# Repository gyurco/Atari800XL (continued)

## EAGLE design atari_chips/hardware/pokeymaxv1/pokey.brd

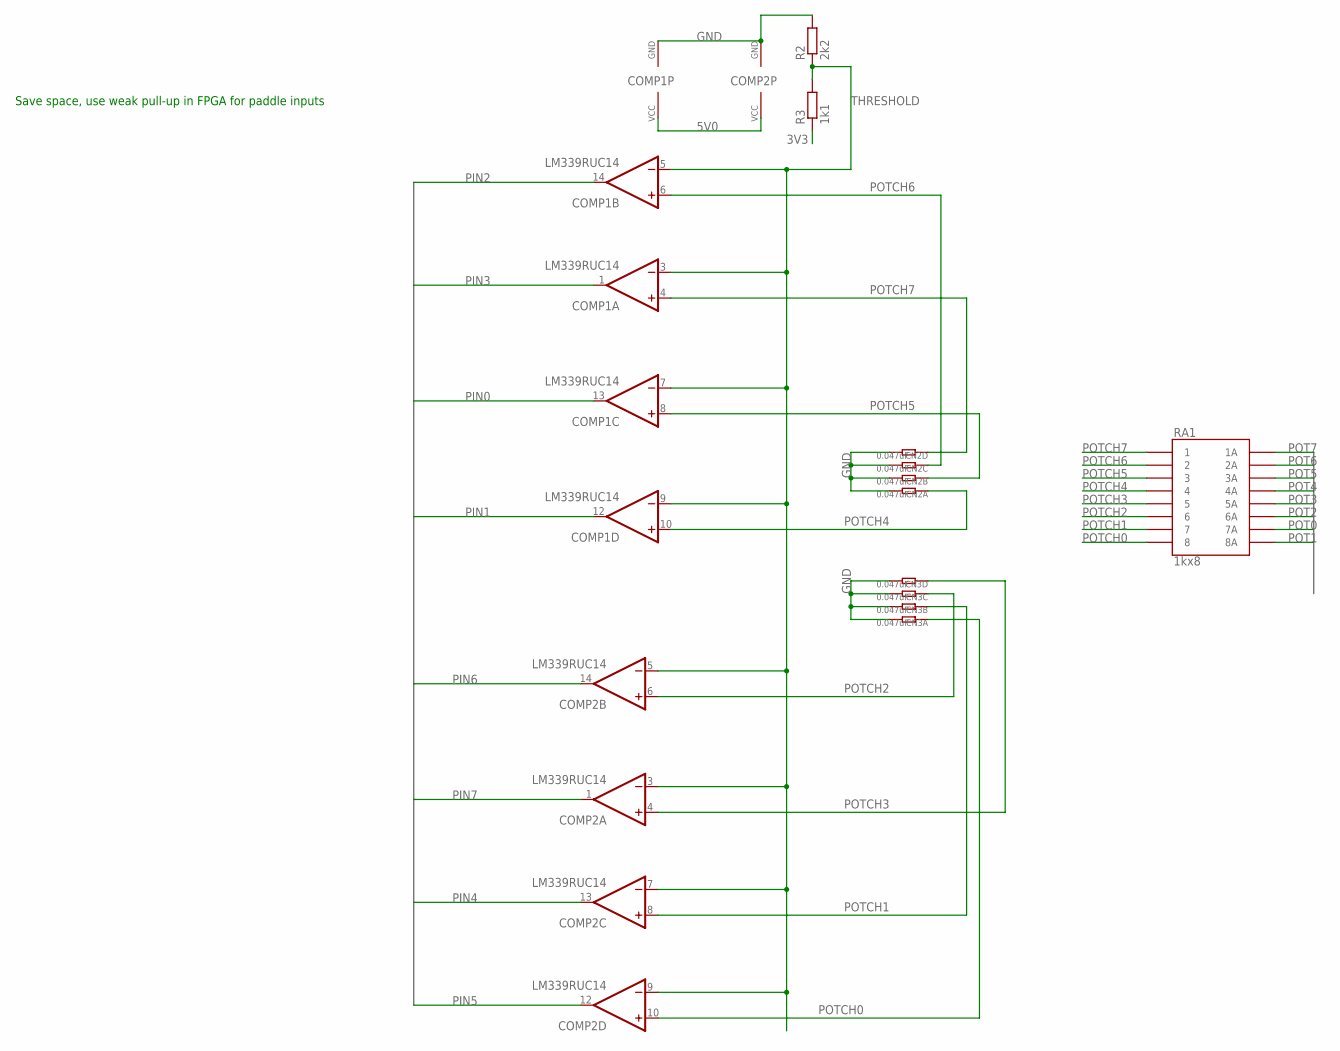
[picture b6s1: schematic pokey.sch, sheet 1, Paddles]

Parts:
CN2, CN3: 0.047uF; R1206-8
COMP1, COMP2: LM339RUC14; RUC14
R2: 2k2; R0603
R3: 1k1; R0603
RA1: 1kx8; CAY16-J8

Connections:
3V3: R3.1; also elsewhere on the board
5V0: COMP1.2 (VCC), COMP2.2 (VCC); also elsewhere on the board
GND: CN2.5 (2), CN2.6 (2), CN2.7 (2), CN2.8 (2), CN3.5 (2), CN3.6 (2), CN3.7 (2), CN3.8 (2), COMP1.11 (GND), COMP2.11 (GND), R2.2; also elsewhere on the board
PIN0: COMP1.13 (OUT); also elsewhere on the board
PIN1: COMP1.12 (OUT); also elsewhere on the board
PIN2: COMP1.14 (OUT); also elsewhere on the board
PIN3: COMP1.1 (OUT); also elsewhere on the board
PIN4: COMP2.13 (OUT); also elsewhere on the board
PIN5: COMP2.12 (OUT); also elsewhere on the board
PIN6: COMP2.14 (OUT); also elsewhere on the board
PIN7: COMP2.1 (OUT); also elsewhere on the board
POT0: RA1.P$10 (7A); also elsewhere on the board
POT1: RA1.P$9 (8A); also elsewhere on the board
POT2: RA1.P$11 (6A); also elsewhere on the board
POT3: RA1.P$12 (5A); also elsewhere on the board
POT4: RA1.P$13 (4A); also elsewhere on the board
POT5: RA1.P$14 (3A); also elsewhere on the board
POT6: RA1.P$15 (2A); also elsewhere on the board
POT7: RA1.P$16 (1A); also elsewhere on the board
POTCH0: CN3.1, COMP2.10 (+IN), RA1.P$8 (8); also elsewhere on the board
POTCH1: CN3.2 (1), COMP2.8 (+IN), RA1.P$7 (7); also elsewhere on the board
POTCH2: CN3.3 (1), COMP2.6 (+IN), RA1.P$6 (6); also elsewhere on the board
POTCH3: CN3.4 (1), COMP2.4 (+IN), RA1.P$5 (5); also elsewhere on the board
POTCH4: CN2.1, COMP1.10 (+IN), RA1.P$4 (4); also elsewhere on the board
POTCH5: CN2.2 (1), COMP1.8 (+IN), RA1.P$3 (3); also elsewhere on the board
POTCH6: CN2.3 (1), COMP1.6 (+IN), RA1.P$2 (2); also elsewhere on the board
POTCH7: CN2.4 (1), COMP1.4 (+IN), RA1.P$1 (1); also elsewhere on the board
THRESHOLD: COMP1.3 (-IN), COMP1.5 (-IN), COMP1.7 (-IN), COMP1.9 (-IN), COMP2.3 (-IN), COMP2.5 (-IN), COMP2.7 (-IN), COMP2.9 (-IN), R2.1, R3.2

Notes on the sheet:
Save space, use weak pull-up in FPGA for paddle inputs

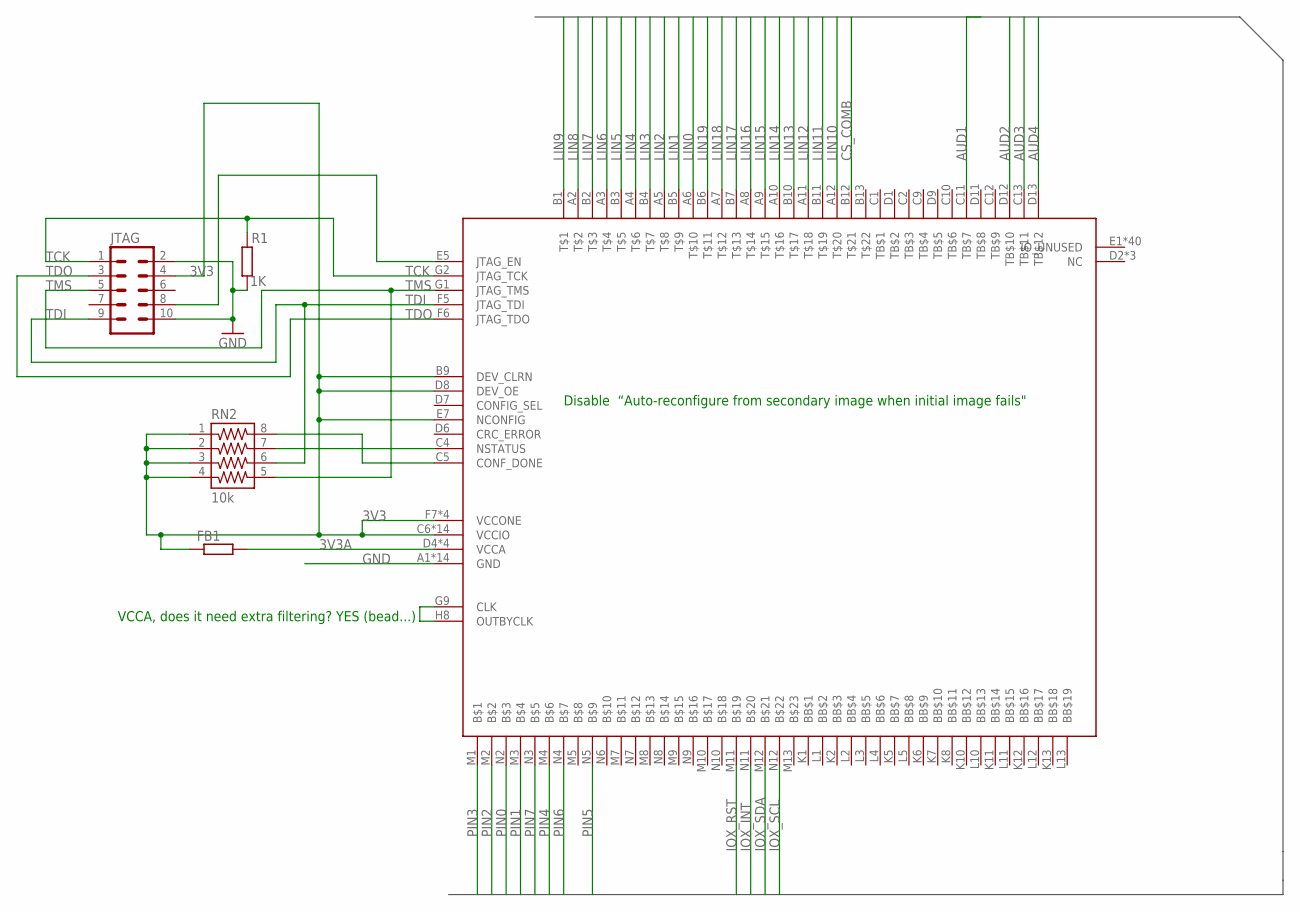
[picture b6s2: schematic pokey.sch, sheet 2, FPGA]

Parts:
FB1: R-EU_R0603; R0603
JTAG: ML10
MAX10: MAX10; U169SMALL
R1: 1K; R0603
RN2: 10k; 742-8

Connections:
3V3: FB1.1, JTAG.4, MAX10.B9 (DEV_CLRN), MAX10.C6 (VCCIO), MAX10.C7 (VCCIO), MAX10.C8 (VCCIO), MAX10.D8 (DEV_OE), MAX10.E7 (NCONFIG), MAX10.F2 (VCCIO), MAX10.F7 (VCCONE), MAX10.F11 (VCCIO), MAX10.G3 (VCCIO), MAX10.G6 (VCCONE), MAX10.G8 (VCCONE), MAX10.G11 (VCCIO), MAX10.H7 (VCCONE), MAX10.H11 (VCCIO), MAX10.J3 (VCCIO), MAX10.J11 (VCCIO), MAX10.K3 (VCCIO), MAX10.L6 (VCCIO), MAX10.L7 (VCCIO), MAX10.L8 (VCCIO), RN2.1, RN2.2, RN2.3, RN2.4; also elsewhere on the board
3V3A: FB1.2, MAX10.D4 (VCCA), MAX10.D10 (VCCA), MAX10.K4 (VCCA), MAX10.K9 (VCCA); also elsewhere on the board
AUD1: MAX10.C11 (TB$7); also elsewhere on the board
AUD2: MAX10.D12 (TB$10); also elsewhere on the board
AUD3: MAX10.C13 (TB$11); also elsewhere on the board
AUD4: MAX10.D13 (TB$12); also elsewhere on the board
CONF_DONE: MAX10.C5 (CONF_DONE), RN2.8
CS_COMB: MAX10.B12; also elsewhere on the board
FAKE_CLK: MAX10.G9 (CLK), MAX10.H8 (OUTBYCLK)
GND: JTAG.2, JTAG.10, MAX10.A1 (GND), MAX10.A13 (GND), MAX10.B8 (GND), MAX10.C3 (GND), MAX10.D5 (GND), MAX10.E11 (GND), MAX10.F3 (GND), MAX10.G7 (GND), MAX10.H12 (GND), MAX10.J4 (GND), MAX10.L9 (GND), MAX10.M6 (GND), MAX10.N1 (GND), MAX10.N13 (GND), R1.2; also elsewhere on the board
IOX_INT: MAX10.N11; also elsewhere on the board
IOX_RST: MAX10.M11; also elsewhere on the board
IOX_SCL: MAX10.N12; also elsewhere on the board
IOX_SDA: MAX10.M12; also elsewhere on the board
JTAGEN: JTAG.8, MAX10.E5 (JTAG_EN)
LIN0: MAX10.A6; also elsewhere on the board
LIN1: MAX10.B5; also elsewhere on the board
LIN2: MAX10.A5; also elsewhere on the board
LIN3: MAX10.B4; also elsewhere on the board
LIN4: MAX10.A4; also elsewhere on the board
LIN5: MAX10.B3; also elsewhere on the board
LIN6: MAX10.A3; also elsewhere on the board
LIN7: MAX10.B2; also elsewhere on the board
LIN8: MAX10.A2; also elsewhere on the board
LIN9: MAX10.B1; also elsewhere on the board
LIN10: MAX10.A12; also elsewhere on the board
LIN11: MAX10.B11; also elsewhere on the board
LIN12: MAX10.A11; also elsewhere on the board
LIN13: MAX10.B10; also elsewhere on the board
LIN14: MAX10.A10; also elsewhere on the board
LIN15: MAX10.A9; also elsewhere on the board
LIN16: MAX10.A8; also elsewhere on the board
LIN17: MAX10.B7; also elsewhere on the board
LIN18: MAX10.A7; also elsewhere on the board
LIN19: MAX10.B6; also elsewhere on the board
NSTATUS: MAX10.C4 (NSTATUS), RN2.7
PIN0: MAX10.N2; also elsewhere on the board
PIN1: MAX10.M3; also elsewhere on the board
PIN2: MAX10.M2; also elsewhere on the board
PIN3: MAX10.M1; also elsewhere on the board
PIN4: MAX10.M4; also elsewhere on the board
PIN5: MAX10.N5; also elsewhere on the board
PIN6: MAX10.N4; also elsewhere on the board
PIN7: MAX10.N3; also elsewhere on the board
TCK: JTAG.1, MAX10.G2 (JTAG_TCK), R1.1
TDI: JTAG.9, MAX10.F5 (JTAG_TDI), RN2.6
TDO: JTAG.3, MAX10.F6 (JTAG_TDO)
TMS: JTAG.5, MAX10.G1 (JTAG_TMS), RN2.5

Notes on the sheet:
VCCA, does it need extra filtering? YES (bead...)
Disable “Auto-reconfigure from secondary image when initial image fails"

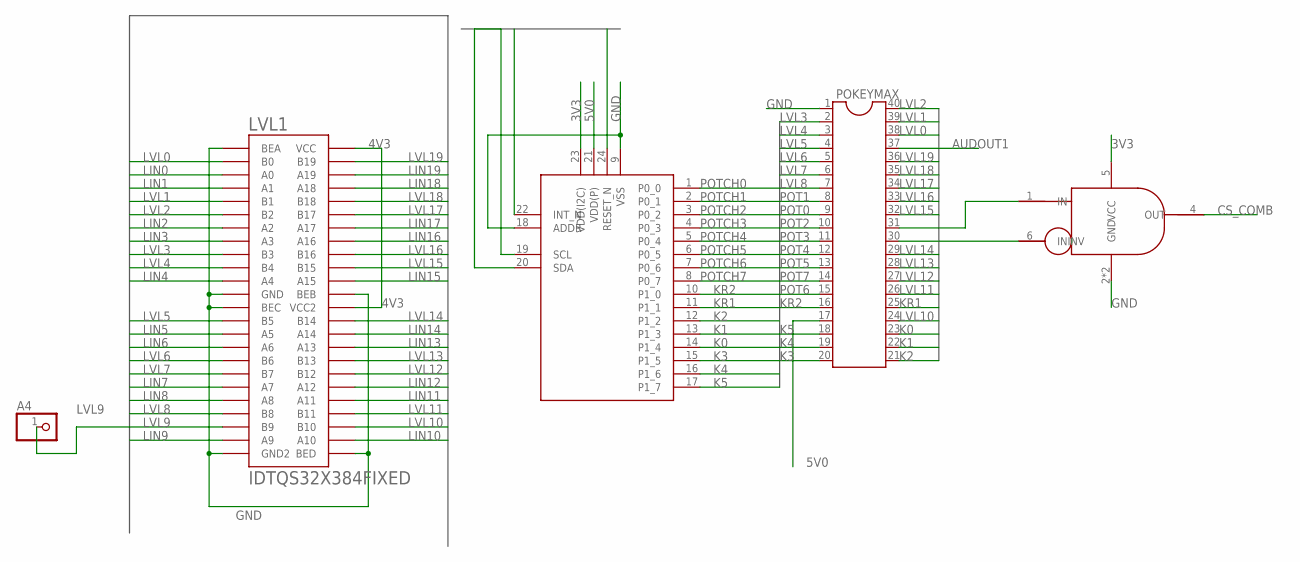
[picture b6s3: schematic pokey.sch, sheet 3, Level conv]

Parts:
A4: PINHD-1X1; 1X01
AND1: AND_INV; SOT-23-6
IOEXT: PCAL6416A; QFN-24
LVL1: IDTQS32X384FIXED; IDTQS32X384_04MM
POKEYMAX: DIL40

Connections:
3V3: AND1.5 (VCC), IOEXT.23 (VDD(I2C)); also elsewhere on the board
4V3: LVL1.P$36 (VCC2), LVL1.P$48 (VCC); also elsewhere on the board
5V0: IOEXT.21 (VDD(P)), POKEYMAX.17; also elsewhere on the board
AUDOUT1: POKEYMAX.37; also elsewhere on the board
CS_COMB: AND1.4 (OUT); also elsewhere on the board
GND: AND1.2 (GND), AND1.3 (GND), IOEXT.9 (VSS), IOEXT.18 (ADDR), LVL1.P$1 (BEA), LVL1.P$12 (GND), LVL1.P$13 (BEC), LVL1.P$24 (GND2), LVL1.P$25 (BED), LVL1.P$37 (BEB), POKEYMAX.1; also elsewhere on the board
IOX_INT: IOEXT.22 (INT_N); also elsewhere on the board
IOX_RST: IOEXT.24 (RESET_N); also elsewhere on the board
IOX_SCL: IOEXT.19 (SCL); also elsewhere on the board
IOX_SDA: IOEXT.20 (SDA); also elsewhere on the board
K0: IOEXT.14 (P1_4), POKEYMAX.23
K1: IOEXT.13 (P1_3), POKEYMAX.22
K2: IOEXT.12 (P1_2), POKEYMAX.21
K3: IOEXT.15 (P1_5), POKEYMAX.20
K4: IOEXT.16 (P1_6), POKEYMAX.19
K5: IOEXT.17 (P1_7), POKEYMAX.18
KR1: IOEXT.11 (P1_1), POKEYMAX.25
KR2: IOEXT.10 (P1_0), POKEYMAX.16
LIN0: LVL1.P$3 (A0); also elsewhere on the board
LIN1: LVL1.P$4 (A1); also elsewhere on the board
LIN2: LVL1.P$7 (A2); also elsewhere on the board
LIN3: LVL1.P$8 (A3); also elsewhere on the board
LIN4: LVL1.P$11 (A4); also elsewhere on the board
LIN5: LVL1.P$15 (A5); also elsewhere on the board
LIN6: LVL1.P$16 (A6); also elsewhere on the board
LIN7: LVL1.P$19 (A7); also elsewhere on the board
LIN8: LVL1.P$20 (A8); also elsewhere on the board
LIN9: LVL1.P$23 (A9); also elsewhere on the board
LIN10: LVL1.P$26 (A10); also elsewhere on the board
LIN11: LVL1.P$29 (A11); also elsewhere on the board
LIN12: LVL1.P$30 (A12); also elsewhere on the board
LIN13: LVL1.P$33 (A13); also elsewhere on the board
LIN14: LVL1.P$34 (A14); also elsewhere on the board
LIN15: LVL1.P$38 (A15); also elsewhere on the board
LIN16: LVL1.P$41 (A16); also elsewhere on the board
LIN17: LVL1.P$42 (A17); also elsewhere on the board
LIN18: LVL1.P$45 (A18); also elsewhere on the board
LIN19: LVL1.P$46 (A19); also elsewhere on the board
LVL0: LVL1.P$2 (B0), POKEYMAX.38
LVL1: LVL1.P$5 (B1), POKEYMAX.39
LVL2: LVL1.P$6 (B2), POKEYMAX.40
LVL3: LVL1.P$9 (B3), POKEYMAX.2
LVL4: LVL1.P$10 (B4), POKEYMAX.3
LVL5: LVL1.P$14 (B5), POKEYMAX.4
LVL6: LVL1.P$17 (B6), POKEYMAX.5
LVL7: LVL1.P$18 (B7), POKEYMAX.6
LVL8: LVL1.P$21 (B8), POKEYMAX.7
LVL9: A4.1, LVL1.P$22 (B9)
LVL10: LVL1.P$27 (B10), POKEYMAX.24
LVL11: LVL1.P$28 (B11), POKEYMAX.26
LVL12: LVL1.P$31 (B12), POKEYMAX.27
LVL13: LVL1.P$32 (B13), POKEYMAX.28
LVL14: LVL1.P$35 (B14), POKEYMAX.29
LVL15: LVL1.P$39 (B15), POKEYMAX.32
LVL16: LVL1.P$40 (B16), POKEYMAX.33
LVL17: LVL1.P$43 (B17), POKEYMAX.34
LVL18: LVL1.P$44 (B18), POKEYMAX.35
LVL19: LVL1.P$47 (B19), POKEYMAX.36
unnamed: AND1.1 (IN), POKEYMAX.31
unnamed: AND1.6 (ININV), POKEYMAX.30
POT0: POKEYMAX.9; also elsewhere on the board
POT1: POKEYMAX.8; also elsewhere on the board
POT2: POKEYMAX.10; also elsewhere on the board
POT3: POKEYMAX.11; also elsewhere on the board
POT4: POKEYMAX.12; also elsewhere on the board
POT5: POKEYMAX.13; also elsewhere on the board
POT6: POKEYMAX.15; also elsewhere on the board
POT7: POKEYMAX.14; also elsewhere on the board
POTCH0: IOEXT.1 (P0_0); also elsewhere on the board
POTCH1: IOEXT.2 (P0_1); also elsewhere on the board
POTCH2: IOEXT.3 (P0_2); also elsewhere on the board
POTCH3: IOEXT.4 (P0_3); also elsewhere on the board
POTCH4: IOEXT.5 (P0_4); also elsewhere on the board
POTCH5: IOEXT.6 (P0_5); also elsewhere on the board
POTCH6: IOEXT.7 (P0_6); also elsewhere on the board
POTCH7: IOEXT.8 (P0_7); also elsewhere on the board

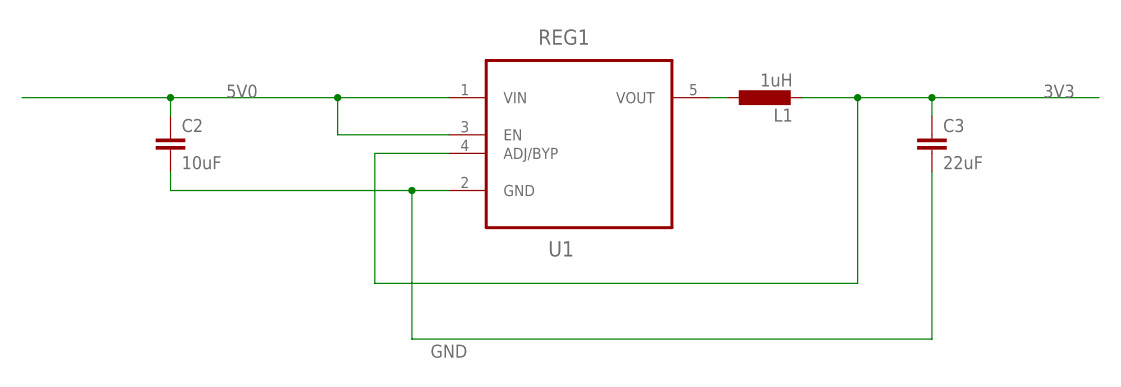
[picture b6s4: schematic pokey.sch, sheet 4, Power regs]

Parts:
C2: 10uF; C0805
C3: 22uF; C0805
L1: 1uH; L3225M
REG1: U1; SOT95P280X145-5N

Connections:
3V3: C3.1, L1.2, REG1.4 (ADJ/BYP); also elsewhere on the board
5V0: C2.1, REG1.1 (VIN), REG1.3 (EN); also elsewhere on the board
GND: C2.2, C3.2, REG1.2 (GND); also elsewhere on the board
unnamed: L1.1, REG1.5 (VOUT)

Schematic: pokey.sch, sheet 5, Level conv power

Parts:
C1: 0.1uF; C0603
D1: 1N4148; SOD123

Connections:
4V3: C1.2, D1.1 (CA); also elsewhere on the board
5V0: D1.2 (AN); also elsewhere on the board
GND: C1.1; also elsewhere on the board

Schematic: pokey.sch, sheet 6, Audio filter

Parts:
AUD: PINHD-1X4; 1X04
CN1: 4.7nF; R1206-8
RN1: 3k3; 742-8

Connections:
AUD1: RN1.1; also elsewhere on the board
AUD2: RN1.2; also elsewhere on the board
AUD3: RN1.3; also elsewhere on the board
AUD4: RN1.4; also elsewhere on the board
AUDOUT1: CN1.5 (2), RN1.8; also elsewhere on the board
AUDOUT2: AUD.3, CN1.6 (2), RN1.7
AUDOUT3: AUD.1, CN1.7 (2), RN1.6
AUDOUT4: AUD.2, CN1.8 (2), RN1.5
GND: AUD.4, CN1.1, CN1.2 (1), CN1.3 (1), CN1.4 (1); also elsewhere on the board

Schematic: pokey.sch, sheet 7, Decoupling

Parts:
C4, C5, C6, C7, C8: 0.1uF; C0603

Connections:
3V3: C4.1, C6.1, C8.1; also elsewhere on the board
3V3A: C5.1; also elsewhere on the board
5V0: C7.1; also elsewhere on the board
GND: C4.2, C5.2, C6.2, C7.2, C8.2; also elsewhere on the board

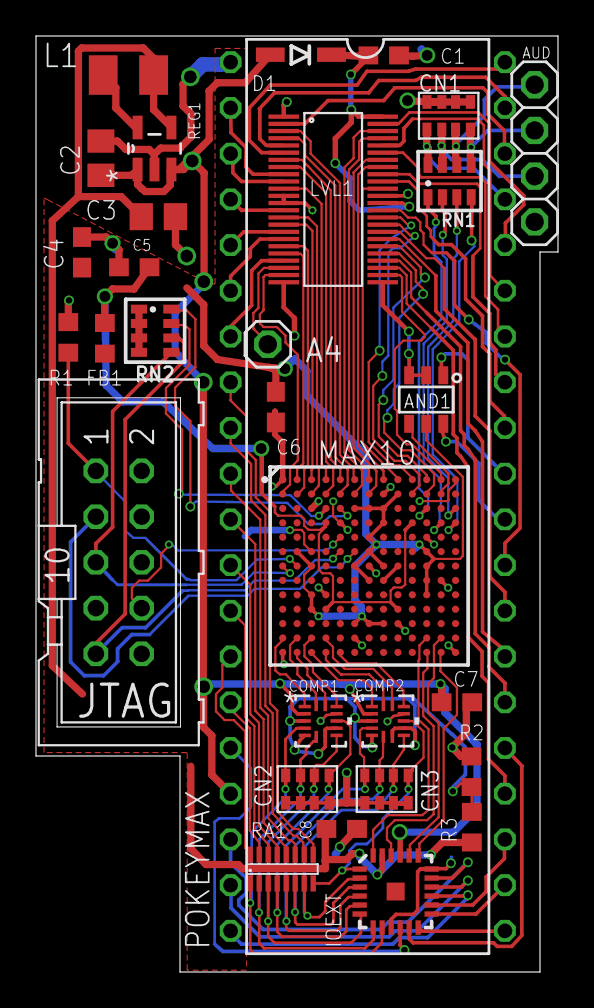
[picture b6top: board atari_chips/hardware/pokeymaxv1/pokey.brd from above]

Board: 2 copper layers, 29.0 x 52.0 mm, 31 parts (0 on the bottom side), 102 nets.

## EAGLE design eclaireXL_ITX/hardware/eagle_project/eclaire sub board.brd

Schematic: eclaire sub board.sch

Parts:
CARTRIDGE_PORT: CARTRIDGE_SOCKET_BARE; CARTRIDGE_SOCKET
H1, H2: MOUNT-PAD-ROUND3.6; 3,6-PAD
H3: MOUNT-PAD-ROUND3.2; 3,2-PAD
PBI_CART_INT: ML40
PBI_PORT: ML50
PF1: 1A; R1206
POWER_IN: USB-B-H
SIO_INT: ML10
SIO_PORT: SIO_JACK
SW1: 450302014072ROCKER2; ROCKER_VERT_SPDT2
U$6: MOLEX_PS

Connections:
5V0: POWER_IN.VBUS, SW1.P$2 (1)
5VMAIN: PF1.1, SW1.P$3 (3), U$6.+
5VOUT: CARTRIDGE_PORT.13 (+5V), PBI_PORT.47, PBI_PORT.48, PF1.2, SIO_PORT.10 (+5V/READY)
A0: CARTRIDGE_PORT.5 (A0), PBI_CART_INT.23, PBI_PORT.3
A1: CARTRIDGE_PORT.4 (A1), PBI_CART_INT.25, PBI_PORT.4
A2: CARTRIDGE_PORT.3 (A2), PBI_CART_INT.27, PBI_PORT.5
A3: CARTRIDGE_PORT.2 (A3), PBI_CART_INT.28, PBI_PORT.6
A4: CARTRIDGE_PORT.C (A4), PBI_CART_INT.26, PBI_PORT.7
A5: CARTRIDGE_PORT.D (A5), PBI_CART_INT.24, PBI_PORT.8
A6: CARTRIDGE_PORT.E (A6), PBI_CART_INT.22, PBI_PORT.9
A7: CARTRIDGE_PORT.F (A7), PBI_CART_INT.20, PBI_PORT.11
A8: CARTRIDGE_PORT.H (A8), PBI_CART_INT.18, PBI_PORT.12
A9: CARTRIDGE_PORT.J (A9), PBI_CART_INT.16, PBI_PORT.13
A10: CARTRIDGE_PORT.P (A10), PBI_CART_INT.5, PBI_PORT.14
A11: CARTRIDGE_PORT.N (A11), PBI_CART_INT.6, PBI_PORT.15
A12: CARTRIDGE_PORT.K (A12), PBI_CART_INT.14, PBI_PORT.16
A13: PBI_CART_INT.34, PBI_PORT.17
A14: PBI_CART_INT.35, PBI_PORT.18
A15: PBI_CART_INT.36, PBI_PORT.20
CASINH_N: PBI_PORT.38
CAS_N: PBI_PORT.41
CCTL_N: CARTRIDGE_PORT.15 (!CCTL), PBI_CART_INT.1
COMMAND: SIO_INT.2, SIO_PORT.7 (COMMAND)
D0: CARTRIDGE_PORT.10 (D0), PBI_CART_INT.13, PBI_PORT.21
D1: CARTRIDGE_PORT.9 (D1), PBI_CART_INT.15, PBI_PORT.22
D2: CARTRIDGE_PORT.8 (D2), PBI_CART_INT.17, PBI_PORT.23
D3: CARTRIDGE_PORT.L (D3), PBI_CART_INT.10, PBI_PORT.24
D4: CARTRIDGE_PORT.6 (D4), PBI_CART_INT.21, PBI_PORT.25
D5: CARTRIDGE_PORT.7 (D5), PBI_CART_INT.19, PBI_PORT.26
D6: CARTRIDGE_PORT.11 (D6), PBI_CART_INT.9, PBI_PORT.27
D7: CARTRIDGE_PORT.M (D7), PBI_CART_INT.8, PBI_PORT.28
EXTSEL_N: PBI_CART_INT.33, PBI_PORT.2
GND: CARTRIDGE_PORT.B (GND), H1.B3,6, H2.B3,6, H3.B3,2, PBI_PORT.1, PBI_PORT.10, PBI_PORT.19, PBI_PORT.29, PBI_PORT.30, PBI_PORT.32, PBI_PORT.42, PBI_PORT.45, PBI_PORT.50, POWER_IN.GND, SIO_PORT.4 (GROUND1), SIO_PORT.6 (GROUND2), U$6.- (--)
IRQ_N: PBI_CART_INT.39, PBI_PORT.35
MIC: PBI_CART_INT.29, PBI_CART_INT.30, PBI_PORT.49, SIO_INT.9, SIO_PORT.11 (AUDIO_INPUT)
MOTOR: SIO_INT.8, SIO_INT.10, SIO_PORT.8 (MOTOR_CONTROL)
MPD_N: PBI_CART_INT.37, PBI_PORT.43
PHI2: CARTRIDGE_PORT.S (PHI2), PBI_CART_INT.2, PBI_PORT.31
PROCEED: SIO_INT.4, SIO_PORT.9 (PROCEED)
RAS_N: PBI_PORT.44
RD4: CARTRIDGE_PORT.A (RD4), PBI_CART_INT.31
RD5: CARTRIDGE_PORT.14 (RD5), PBI_CART_INT.3
RDY_N: PBI_PORT.36
REF_N: PBI_CART_INT.38, PBI_PORT.40
RST_N: PBI_CART_INT.40, PBI_PORT.34
RW_N: CARTRIDGE_PORT.R (R/!W), PBI_CART_INT.4, PBI_PORT.46
S4_N: CARTRIDGE_PORT.1 (!S4), PBI_CART_INT.32
S5_N: CARTRIDGE_PORT.12 (!S5), PBI_CART_INT.7
SIO_CLOCKIN: SIO_INT.6, SIO_PORT.1 (CLOCK_INPUT)
SIO_CLOCKOUT: SIO_INT.1, SIO_PORT.2 (CLOCK_OUTPUT)
SIO_IN: SIO_INT.3, SIO_PORT.3 (DATA_INPUT)
SIO_IRQ: SIO_INT.5, SIO_PORT.13 (INTERRUPT)
SIO_OUT: SIO_INT.7, SIO_PORT.5 (DATA_OUTPUT)

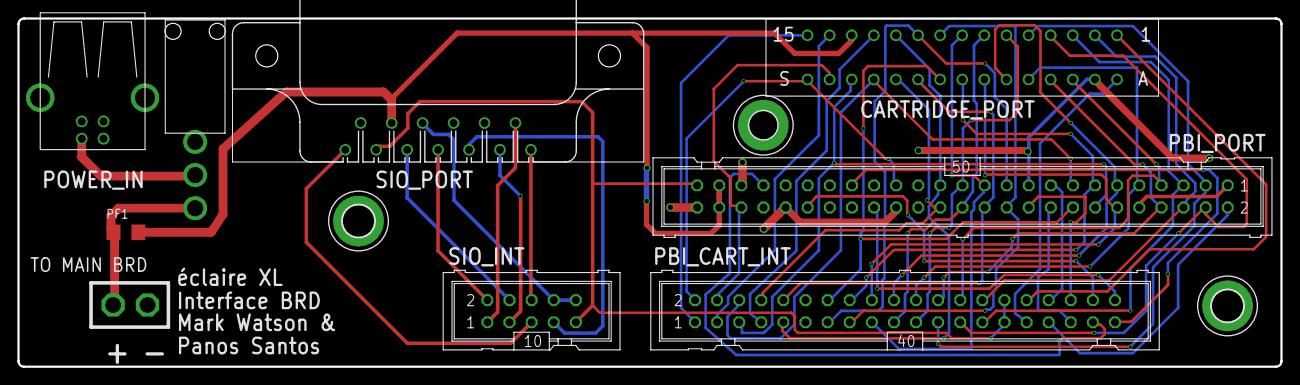
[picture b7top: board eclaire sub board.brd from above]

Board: 4 copper layers, 145.1 x 40.0 mm, 12 parts (0 on the bottom side), 49 nets.

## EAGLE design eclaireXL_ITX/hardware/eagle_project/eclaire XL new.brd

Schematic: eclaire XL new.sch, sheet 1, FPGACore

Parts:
C17, C27: 0.1uF; C0805
JTAG: ML10
R12, R17, R18: 10k; M0805
R14: 2K 1%; M0805
R15, R16: 4.7k; M0805
R19, R21: 1k-10k; M0805
R20: 1k; M0805
R25A: 560; M0805
RESET: RESET; JP1
RESET_LED: RESET; JP1
SPI: U6; EPCS_BOTH
U$1: U7; CYCLONEVF484V2
XTL_50MHZ: 50MHz; SG-636

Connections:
1V1: U$1.J4 (VCC), U$1.J10 (VCC), U$1.J12 (VCC), U$1.J14 (VCC), U$1.J16 (VCC), U$1.K3 (VCC), U$1.K5 (VCC), U$1.K11 (VCC), U$1.K13 (VCC), U$1.K15 (VCC), U$1.L4 (VCC), U$1.L10 (VCC), U$1.L12 (VCC), U$1.L14 (VCC), U$1.L16 (VCC), U$1.M11 (VCC), U$1.M13 (VCC), U$1.M15 (VCC), U$1.N4 (VCC), U$1.N10 (VCC), U$1.N12 (VCC), U$1.N14 (VCC), U$1.P3 (VCC), U$1.P11 (VCC), U$1.P13 (VCC), U$1.P15 (VCC); also elsewhere on the board
2V5: U$1.A3 (VCCBAT), U$1.D11 (VCC_AUX), U$1.D18 (VCC_AUX), U$1.E6 (VCC_AUX), U$1.F4 (VCCA_FPLL), U$1.H19 (VCCA_FPLL), U$1.M3 (VCCA_FPLL), U$1.T3 (VCCA_FPLL), U$1.T5 (VCCA_FPLL), U$1.U18 (VCCA_FPLL), U$1.W7 (VCC_AUX), U$1.W13 (VCC_AUX), U$1.W18 (VCC_AUX); also elsewhere on the board
3V3: C17.1, C27.1, JTAG.4, R12.2, R15.1, R16.1, R17.2, R18.2, R19.2, R21.2, SPI.8 (VCC), SPI.L$2 (VCC), U$1.A6 (VCCIO), U$1.A16 (VCCIO), U$1.AA16 (VCCIO), U$1.AA21 (VCCIO), U$1.AB16 (VREF), U$1.B8 (VREF), U$1.B19 (VCCIO), U$1.C7 (VCCIO), U$1.C10 (VCCPGM), U$1.C12 (VCCIO), U$1.C14 (VREF), U$1.C22 (VCCIO), U$1.D4 (VCCIO), U$1.D8 (VCCPGM), U$1.D14 (VCCPGM), U$1.D15 (VCCIO), U$1.D16 (VCCPGM), U$1.E1 (VCCPGM), U$1.E8 (VCCIO), U$1.E11 (VCCPGM), U$1.E18 (VCCIO), U$1.F3 (MSEL_4), U$1.F8 (VCCPGM), U$1.F11 (VCCIO), U$1.F21 (VCCIO), U$1.G7 (VCCIO), U$1.G14 (VCCIO), U$1.H17 (VCCIO), U$1.J1 (VCCIO), U$1.J2 (VCCPGM), U$1.J6 (MSEL_1), U$1.K18 (VCCIO), U$1.L6 (MSEL_0), U$1.L20 (VREF), U$1.M17 (VCCPGM), U$1.M19 (VCCIO), U$1.N18 (VCCPGM), U$1.P20 (VCCIO), U$1.P21 (VCCPGM), U$1.R1 (VCCIO), U$1.R2 (VCCPGM), U$1.R8 (VCCIO), U$1.R18 (VCCIO), U$1.R19 (VCCPGM), U$1.R20 (VREF), U$1.T6 (VCCIO), U$1.T11 (VCCIO), U$1.U14 (VCCIO), U$1.U19 (VCCIO), U$1.V8 (VCCPGM), U$1.W1 (VREF), U$1.W6 (VCCPGM), U$1.W10 (VCCIO), U$1.W11 (VCCPGM), U$1.W12 (VCCPGM), U$1.W14 (VCCPGM), U$1.W15 (VCCIO), U$1.W17 (VCCPGM), U$1.W20 (VCCIO), U$1.Y4 (VCCIO), U$1.Y7 (VREF), U$1.Y8 (VCCIO), U$1.Y12 (VREF), U$1.Y13 (VCCIO), XTL_50MHZ.P$1 (CON), XTL_50MHZ.P$4 (VDD); also elsewhere on the board
5V0: R25A.1; also elsewhere on the board
A0: U$1.R6; also elsewhere on the board
A1: U$1.R5; also elsewhere on the board
A2: U$1.T7; also elsewhere on the board
A3: U$1.U6; also elsewhere on the board
A4: U$1.Y10; also elsewhere on the board
A5: U$1.U10; also elsewhere on the board
A6: U$1.T10; also elsewhere on the board
A7: U$1.AA9; also elsewhere on the board
A8: U$1.W9; also elsewhere on the board
A9: U$1.Y9; also elsewhere on the board
A10: U$1.R7; also elsewhere on the board
A11: U$1.V9; also elsewhere on the board
A12: U$1.T9; also elsewhere on the board
AUDIO_LEFT: U$1.U13; also elsewhere on the board
AUDIO_RIGHT: U$1.T13; also elsewhere on the board
BA0: U$1.P7; also elsewhere on the board
BA1: U$1.P6; also elsewhere on the board
CAS_N: U$1.N8; also elsewhere on the board
CKE: U$1.AB8; also elsewhere on the board
COMMAND: U$1.AB11; also elsewhere on the board
CONFIG_N: R12.1, RESET.2, U$1.A4 (CONFIG_N)
CONF_DONE: R18.1, U$1.K6 (CONF_DONE)
CS_N: U$1.P8; also elsewhere on the board
DQ0: U$1.K7; also elsewhere on the board
DQ1: U$1.K9; also elsewhere on the board
DQ2: U$1.J7; also elsewhere on the board
DQ3: U$1.J8; also elsewhere on the board
DQ4: U$1.L8; also elsewhere on the board
DQ5: U$1.L7; also elsewhere on the board
DQ6: U$1.M8; also elsewhere on the board
DQ7: U$1.M7; also elsewhere on the board
DQ8: U$1.W8; also elsewhere on the board
DQ9: U$1.T8; also elsewhere on the board
DQ10: U$1.AB7; also elsewhere on the board
DQ11: U$1.AA7; also elsewhere on the board
DQ12: U$1.U7; also elsewhere on the board
DQ13: U$1.AB6; also elsewhere on the board
DQ14: U$1.V6; also elsewhere on the board
DQ15: U$1.AB5; also elsewhere on the board
GND: C17.2, C27.2, JTAG.2, JTAG.10, R14.2, R20.2, RESET.1, RESET_LED.2, SPI.4 (GND), SPI.L$10 (GND), U$1.A2 (MSEL_2), U$1.A11 (GND), U$1.A21 (GND), U$1.AA3 (GND), U$1.AA4 (GND), U$1.AA6 (GND), U$1.AA11 (GND), U$1.AB1 (GND), U$1.AB2 (GND), U$1.AB9 (GND), U$1.AB14 (GND), U$1.AB19 (GND), U$1.B1 (GND), U$1.B2 (GND), U$1.B9 (GND), U$1.B14 (GND), U$1.C3 (GND), U$1.C4 (GND), U$1.C5 (GND), U$1.C17 (GND), U$1.D1 (GND), U$1.D2 (GND), U$1.D5 (GND), U$1.D10 (GND), U$1.D20 (GND), U$1.E3 (GND), U$1.E4 (GND), U$1.E5 (MSEL_3), U$1.E13 (GND), U$1.F1 (GND), U$1.F2 (GND), U$1.F5 (GND), U$1.F6 (GND), U$1.F16 (GND), U$1.F17 (GND), U$1.G3 (GND), U$1.G4 (GND), U$1.G5 (CE_N), U$1.G9 (GND), U$1.G19 (GND), U$1.H1 (GND), U$1.H2 (GND), U$1.H3 (GND), U$1.H4 (GND), U$1.H7 (GND), U$1.H12 (GND), U$1.H15 (GND), U$1.H22 (GND), U$1.J3 (GND), U$1.J5 (GND), U$1.J15 (GND), U$1.J20 (GND), U$1.K1 (GND), U$1.K2 (GND), U$1.K4 (GND), U$1.K8 (GND), U$1.K10 (GND), U$1.K12 (GND), U$1.K14 (GND), U$1.L3 (GND), U$1.L5 (GND), U$1.L11 (GND), U$1.L13 (GND), U$1.L15 (GND), U$1.L21 (GND), U$1.M1 (GND), U$1.M2 (GND), U$1.M4 (GND), U$1.M10 (GND), U$1.M12 (GND), U$1.M14 (GND), U$1.N3 (GND), U$1.N5 (GND), U$1.N7 (GND), U$1.N11 (GND), U$1.N13 (GND), U$1.N15 (GND), U$1.N17 (GND), U$1.N22 (GND), U$1.P1 (GND), U$1.P2 (GND), U$1.P4 (GND), U$1.P10 (GND), U$1.R3 (GND), U$1.R13 (GND), U$1.T1 (GND), U$1.T2 (GND), U$1.T16 (GND), U$1.T21 (GND), U$1.U3 (GND), U$1.U4 (GND), U$1.U5 (GND), U$1.U9 (GND), U$1.V1 (GND), U$1.V2 (GND), U$1.V4 (GND), U$1.V7 (GND), U$1.V12 (GND), U$1.V17 (GND), U$1.V22 (GND), U$1.W3 (GND), U$1.W4 (GND), U$1.Y1 (GND), U$1.Y2 (GND), U$1.Y5 (GND), U$1.Y18 (GND), XTL_50MHZ.P$2 (VSS); also elsewhere on the board
GPIOA0: U$1.F15; also elsewhere on the board
GPIOA1: U$1.B16; also elsewhere on the board
GPIOA2: U$1.C16; also elsewhere on the board
GPIOA3: U$1.G17; also elsewhere on the board
GPIOA4: U$1.G16; also elsewhere on the board
GPIOA5: U$1.J18; also elsewhere on the board
GPIOA6: U$1.J17; also elsewhere on the board
GPIOA7: U$1.K21; also elsewhere on the board
GPIOA8: U$1.K20; also elsewhere on the board
GPIOA9: U$1.K16; also elsewhere on the board
GPIOA10: U$1.L19; also elsewhere on the board
GPIOA11: U$1.L17; also elsewhere on the board
GPIOA12: U$1.M21; also elsewhere on the board
GPIOA13: U$1.M20; also elsewhere on the board
GPIOA14: U$1.N21; also elsewhere on the board
GPIOA15: U$1.N20; also elsewhere on the board
GPIOA16: U$1.P22; also elsewhere on the board
GPIOA17: U$1.P19; also elsewhere on the board
GPIOA18: U$1.P16; also elsewhere on the board
GPIOA19: U$1.R21; also elsewhere on the board
GPIOA20: U$1.R16; also elsewhere on the board
GPIOA21: U$1.T19; also elsewhere on the board
GPIOA22: U$1.T18; also elsewhere on the board
GPIOA23: U$1.U22; also elsewhere on the board
GPIOA24: U$1.U20; also elsewhere on the board
GPIOA25: U$1.V19; also elsewhere on the board
GPIOA26: U$1.W22; also elsewhere on the board
GPIOA27: U$1.Y22; also elsewhere on the board
GPIOA28: U$1.AA22; also elsewhere on the board
GPIOA29: U$1.AB21; also elsewhere on the board
GPIOA30: U$1.AA20; also elsewhere on the board
GPIOA31: U$1.AA19; also elsewhere on the board
GPIOA32: U$1.Y19; also elsewhere on the board
GPIOA33: U$1.AA18; also elsewhere on the board
GPIOA34: U$1.AB17; also elsewhere on the board
GPIOA35: U$1.U17; also elsewhere on the board
GPIOB0: U$1.G15; also elsewhere on the board
GPIOB1: U$1.E16; also elsewhere on the board
GPIOB2: U$1.D17; also elsewhere on the board
GPIOB3: U$1.G18; also elsewhere on the board
GPIOB4: U$1.H18; also elsewhere on the board
GPIOB5: U$1.J19; also elsewhere on the board
GPIOB6: U$1.K22; also elsewhere on the board
GPIOB7: U$1.K19; also elsewhere on the board
GPIOB8: U$1.K17; also elsewhere on the board
GPIOB9: U$1.L22; also elsewhere on the board
GPIOB10: U$1.L18; also elsewhere on the board
GPIOB11: U$1.M22; also elsewhere on the board
GPIOB12: U$1.M18; also elsewhere on the board
GPIOB13: U$1.M16; also elsewhere on the board
GPIOB14: U$1.N19; also elsewhere on the board
GPIOB15: U$1.N16; also elsewhere on the board
GPIOB16: U$1.P18; also elsewhere on the board
GPIOB17: U$1.P17; also elsewhere on the board
GPIOB18: U$1.R22; also elsewhere on the board
GPIOB19: U$1.R17; also elsewhere on the board
GPIOB20: U$1.T22; also elsewhere on the board
GPIOB21: U$1.T20; also elsewhere on the board
GPIOB22: U$1.T17; also elsewhere on the board
GPIOB23: U$1.U21; also elsewhere on the board
GPIOB24: U$1.V21; also elsewhere on the board
GPIOB25: U$1.V20; also elsewhere on the board
GPIOB26: U$1.W21; also elsewhere on the board
GPIOB27: U$1.Y21; also elsewhere on the board
GPIOB28: U$1.AB22; also elsewhere on the board
GPIOB29: U$1.AB20; also elsewhere on the board
GPIOB30: U$1.Y20; also elsewhere on the board
GPIOB31: U$1.W19; also elsewhere on the board
GPIOB32: U$1.AB18; also elsewhere on the board
GPIOB33: U$1.V18; also elsewhere on the board
GPIOB34: U$1.AA17; also elsewhere on the board
GPIOB35: U$1.Y17; also elsewhere on the board
GPIOC8: U$1.F13; also elsewhere on the board
GPIOC9: U$1.G13; also elsewhere on the board
GPIOC10: U$1.A14; also elsewhere on the board
GPIOC11: U$1.E14; also elsewhere on the board
GPIOC12: U$1.F14; also elsewhere on the board
GPIOC13: U$1.H14; also elsewhere on the board
GPIOC14: U$1.A15; also elsewhere on the board
GPIOC15: U$1.B15; also elsewhere on the board
GPIOC16: U$1.E15; also elsewhere on the board
GPIOC17: U$1.C15; also elsewhere on the board
GPIOC18: U$1.Y16; also elsewhere on the board
GPIOC19: U$1.V16; also elsewhere on the board
GPIOC20: U$1.W16; also elsewhere on the board
GPIOC21: U$1.U16; also elsewhere on the board
GPIOC22: U$1.AB15; also elsewhere on the board
GPIOC23: U$1.AA15; also elsewhere on the board
GPIOC24: U$1.V15; also elsewhere on the board
GPIOC25: U$1.Y15; also elsewhere on the board
GPIOC26: U$1.U15; also elsewhere on the board
GPIOC27: U$1.T15; also elsewhere on the board
GPIOC28: U$1.AA14; also elsewhere on the board
GPIOC29: U$1.V14; also elsewhere on the board
GPIOC30: U$1.Y14; also elsewhere on the board
GPIOC31: U$1.T14; also elsewhere on the board
GPIOC32: U$1.R14; also elsewhere on the board
GPIOC33: U$1.AB13; also elsewhere on the board
GPIOC34: U$1.AA13; also elsewhere on the board
GPIOC35: U$1.V13; also elsewhere on the board
HSYNC: U$1.C11; also elsewhere on the board
MOTOR_RAW: U$1.Y11; also elsewhere on the board
unnamed: SPI.6 (SCK), SPI.L$16 (SCK), U$1.V3 (AS_DCLK)
unnamed: SPI.1 (~CS), SPI.L$7 (~CS), U$1.R4 (AS_CSO_N)
unnamed: SPI.2 (SO), SPI.L$8 (SO), U$1.AB3 (AS_DATA1)
unnamed: SPI.5 (SI), SPI.L$15 (SI), U$1.AB4 (AS_DATA0)
unnamed: R16.2, SPI.3 (~WP), SPI.L$9 (~WP)
unnamed: R15.2, SPI.7 (~HOLD), SPI.L$1 (~HOLD)
unnamed: U$1.H16 (CLK), XTL_50MHZ.P$3 (OUT)
unnamed: R25A.2, RESET_LED.1
PROCEED: U$1.U11; also elsewhere on the board
RAS_N: U$1.N6; also elsewhere on the board
RREF_TL: R14.1, U$1.A1 (RREF_TL)
SCL: U$1.G6; also elsewhere on the board
SDA: U$1.H6; also elsewhere on the board
SDRAM_CLK: U$1.AA8; also elsewhere on the board
SDRAM_LDQM: U$1.M6; also elsewhere on the board
SDRAM_UDQM: U$1.U8; also elsewhere on the board
SD_CS: U$1.D12; also elsewhere on the board
SD_DAT1: U$1.A13; also elsewhere on the board
SD_DAT2: U$1.B12; also elsewhere on the board
SD_DETECT: U$1.E12; also elsewhere on the board
SD_MISO: U$1.C13; also elsewhere on the board
SD_MOSI: U$1.F12; also elsewhere on the board
SD_SCK: U$1.B13; also elsewhere on the board
SD_WRITEPROTECT: U$1.D13; also elsewhere on the board
SIO_CLOCKIN: U$1.AB12; also elsewhere on the board
SIO_CLOCKOUT: U$1.AA12; also elsewhere on the board
SIO_IN: U$1.U12; also elsewhere on the board
SIO_IRQ: U$1.T12; also elsewhere on the board
SIO_OUT: U$1.R12; also elsewhere on the board
STATUS_N: R17.1, U$1.H5 (STATUS_N)
TCK: JTAG.1, R20.1, U$1.V5 (JTAG_TCK)
TDI: JTAG.9, R21.1, U$1.W5 (JTAG_TDI)
TDO: JTAG.3, U$1.M5 (JTAG_TDO)
TMS: JTAG.5, R19.1, U$1.P5 (JTAG_TMS)
USB1DM: U$1.AA10; also elsewhere on the board
USB1DP: U$1.V10; also elsewhere on the board
USB2DM: U$1.R11; also elsewhere on the board
USB2DP: U$1.AB10; also elsewhere on the board
VGA_B0: U$1.E9; also elsewhere on the board
VGA_B1: U$1.F9; also elsewhere on the board
VGA_B2: U$1.A10; also elsewhere on the board
VGA_B3: U$1.B10; also elsewhere on the board
VGA_B4: U$1.E10; also elsewhere on the board
VGA_B5: U$1.F10; also elsewhere on the board
VGA_B6: U$1.G10; also elsewhere on the board
VGA_B7: U$1.B11; also elsewhere on the board
VGA_BLANK_N: U$1.C9; also elsewhere on the board
VGA_CLK: U$1.G11; also elsewhere on the board
VGA_G0: U$1.D7; also elsewhere on the board
VGA_G1: U$1.F7; also elsewhere on the board
VGA_G2: U$1.A8; also elsewhere on the board
VGA_G3: U$1.G8; also elsewhere on the board
VGA_G4: U$1.C8; also elsewhere on the board
VGA_G5: U$1.H8; also elsewhere on the board
VGA_G6: U$1.A9; also elsewhere on the board
VGA_G7: U$1.D9; also elsewhere on the board
VGA_R0: U$1.A5; also elsewhere on the board
VGA_R1: U$1.B5; also elsewhere on the board
VGA_R2: U$1.B6; also elsewhere on the board
VGA_R3: U$1.D6; also elsewhere on the board
VGA_R4: U$1.C6; also elsewhere on the board
VGA_R5: U$1.A7; also elsewhere on the board
VGA_R6: U$1.B7; also elsewhere on the board
VGA_R7: U$1.E7; also elsewhere on the board
VSYNC: U$1.H11; also elsewhere on the board
WE_N: U$1.N9; also elsewhere on the board

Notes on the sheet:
10011 AS 1x/4x
JTAG also used to program AS via special core

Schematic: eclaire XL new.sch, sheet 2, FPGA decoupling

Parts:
C18: 2.2uF; C0805
C42, C49: 0.01uF; C0805
C43, C47, C50: 0.022uF; C0805
C44, C48: 10uF; C0805
C45, C46: 0.047uF; C0805
C51: 0.0047uF; C0805

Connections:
1V1: C45.2, C46.2, C48.2; also elsewhere on the board
2V5: C18.2, C47.2, C51.2; also elsewhere on the board
3V3: C42.1, C43.1, C44.1, C49.1, C50.1; also elsewhere on the board
GND: C18.1, C42.2, C43.2, C44.2, C45.1, C46.1, C47.1, C48.1, C49.2, C50.2, C51.1; also elsewhere on the board

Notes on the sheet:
Values from the Altera PDN spreadsheet. 400mA 1.1V, 200mA 2.5V and 700mA 3.3V.
